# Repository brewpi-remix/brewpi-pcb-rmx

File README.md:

# 

*[@LBussy](https://github.com/lbussy)'s forks of the original [BrewPi Project](https://github.com/BrewPi)*.  This project has a new website, please also visit https://www.brewpiremix.com.  All files will remain here, the website is just to make it easier for me to keep current information available.

# BrewPi Remix Printed Circuit Board Eagle Files

This repository contains the Eagle files for printed circuit boards supporting [BrewPi Remix](https://www.brewpi.com/this-is-brewpi-0-2/).

## Boards Provided
Within this repository are:

- ESP8266 Boards (Supporting @Thorrak's [ESP8266 BrewPi Controllers](https://github.com/thorrak/brewpi-esp8266))
  - Wemos D1 breakout supporting BrewPi Remix or Fermentrack using @Thorrak's [ESP8266 firmware](https://github.com/thorrak/brewpi-esp8266)
  - RJ-45 breakout board, supporting ESP8266 controllers connected via straight-throgh RJ-45 (i,e, Ethernet) cables
- Arduino Uno shield supporting BrewPi Remix RevC as well as I2C
  - Rotary Encoder breakout to facilitate connecting a rotary encoder with DuPont wires
  - Breakout board, mostly for bench work, providing all possible connections via screw terminals as well as DuPont connections, plus heat/cool LED indicators

## Boards Manufacture
You may order boards for manufacture directly from these links:
- Arduino Shield [From PCBs.io](https://PCBs.io/share/zdeBw)
- Wemos D1 breakout [From PCBs.io](https://PCBs.io/share/z5JLZ)
- Breakout Board [From PCBs.io](https://PCBs.io/share/zvpLA)
- Rotary Encoder Breakout Board [From PCBs.io](https://PCBs.io/share/rJPlG)

## Modifying These Files
If you would like to personalize these board designs, you may modify them with [Autodesk's EAGLE](https://www.autodesk.com/products/eagle/overview). EAGLE is a scriptable electronic design automation (EDA) application with schematic capture, printed circuit board (PCB) layout, auto-router and computer-aided manufacturing (CAM) features. EAGLE stands for Easily Applicable Graphical Layout Editor and is developed by CadSoft Computer GmbH. The company was acquired by Autodesk Inc. in 2016.  

The program supports Windows, Linux, and Mac OS X.  EAGLE is available in a [free version](https://www.autodesk.com/products/eagle/free-download), as well as a [subscription-based version with more features](https://www.autodesk.com/products/eagle/compare).

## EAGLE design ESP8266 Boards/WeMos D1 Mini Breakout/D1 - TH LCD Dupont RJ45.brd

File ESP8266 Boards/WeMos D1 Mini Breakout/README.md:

# 

# Wemos D1 Mini BrewPi Breakout

A Wemos D1 Mini breakout board for BrewPi-derivative ESP8266 projects. No third-party level shifter is required.  Through-hole components only for ease of assembly.

[Order from OshPark](https://oshpark.com/shared_projects/YLXZEzde):

- 2 layer board of 1.74 x 1.74 inches (44.2 x 44.1 mm) 
- $15.10 per set of 3

| Top View          | Bottom View          |
| ----------------- |:--------------------:|
| ![Board Top][top] | ![Board Bottom][bot] |

[top]: Top.png "Board Top"
[bot]: Bottom.png "Board Bottom"

## BOM (controller/shield only):

- 1 x [PCB Shield](https://oshpark.com/shared_projects/YLXZEzde) (this project)
- 1 x [Wemos D1 Mini](https://www.aliexpress.com/item/32688079351.html?spm=a2g0o.productlist.0.0.2dcf3152g4UkxV&algo_pvid=be694029-b1d5-44b7-b733-20b8c0f6ba9a&algo_expid=be694029-b1d5-44b7-b733-20b8c0f6ba9a-0&btsid=3b4ec2af-8a5e-4c59-9e85-bb2bdb771ffd&ws_ab_test=searchweb0_0,searchweb201602_1,searchweb201603_52_) (U1)
- 2 x Male 8-pin header (comes with controller)
- 2 x Female 8-pin header (comes with controller)
- 2 x [1.0uF Capacitor](https://www.mouser.com/ProductDetail/KEMET/C320C105K5R5TA?qs=sGAEpiMZZMt3KoXD5rJ2N0CWo9MbFM%2FuWljjm75KZzs%3D) (C1, C3)
- 2 x [0.1uF Capacitor](https://www.mouser.com/ProductDetail/KEMET/C320C104K3R5TA?qs=sGAEpiMZZMt3KoXD5rJ2N4ZXb0dQpKOeXkTyt%2FbcGss%3D) (C2, C4)
- 2 x [2N7000 N-Channel MOSFET](https://www.mouser.com/ProductDetail/ON-Semiconductor/2N7000?qs=sGAEpiMZZMshyDBzk1%2FWi9bHELEahoDnY1fyKF6A6Ko%3D) (Q1, Q2)
- 5 x [10kΩ 1/4-Watt Resistor](https://www.mouser.com/ProductDetail/KOA-Speer/CF1-4CT52R103J?qs=sGAEpiMZZMtlubZbdhIBIG%252BgbQse942Boczpyiowqgc%3D) (R1-R4)
- 1 x [2.2kΩ 1/4-Watt Resistor](https://www.mouser.com/ProductDetail/KOA-Speer/CF1-4CT52R222J?qs=sGAEpiMZZMu61qfTUdNhGx20sZYqUI%252BADLaC9a%252B2%2Flg%3D) (R5)
- 1 x [Wago 2-terminal Screw Clamp](https://www.aliexpress.com/item/32700056337.html) (PWR)
- 1 x [RJ45 Modular Jack w/no shield](https://www.aliexpress.com/item/32736146888.html) (J1)
- 2 x [4-pin DuPont Header](https://www.aliexpress.com/item/32670112443.html?spm=a2g0o.productlist.0.0.b4045bcffb2Q4C&algo_pvid=e9508115-148b-4d72-a7a3-4e45d189d5c7&algo_expid=e9508115-148b-4d72-a7a3-4e45d189d5c7-12&btsid=35f3875d-d1f0-4b92-9a59-406a3faaa4ef&ws_ab_test=searchweb0_0,searchweb201602_1,searchweb201603_52) (RELAY, LCD)
- 1 x [3-pin DuPont Header](https://www.aliexpress.com/item/32670112443.html?spm=a2g0o.productlist.0.0.b4045bcffb2Q4C&algo_pvid=e9508115-148b-4d72-a7a3-4e45d189d5c7&algo_expid=e9508115-148b-4d72-a7a3-4e45d189d5c7-12&btsid=35f3875d-d1f0-4b92-9a59-406a3faaa4ef&ws_ab_test=searchweb0_0,searchweb201602_1,searchweb201603_52) (PWR)
- 1 x [2-pin DuPont Header](https://www.aliexpress.com/item/32670112443.html?spm=a2g0o.productlist.0.0.b4045bcffb2Q4C&algo_pvid=e9508115-148b-4d72-a7a3-4e45d189d5c7&algo_expid=e9508115-148b-4d72-a7a3-4e45d189d5c7-12&btsid=35f3875d-d1f0-4b92-9a59-406a3faaa4ef&ws_ab_test=searchweb0_0,searchweb201602_1,searchweb201603_52) (PWR)

## Board Manufacture

You may order this board for manufacture directly from [PCBs.io](https://PCBs.io/share/z5JLZ).

## 3D-Printed Case

See [this case](https://www.thingiverse.com/thing:2874176) from Thorrak for a case you can print.

## Modifying These Files

If you would like to personalize these board designs, you may modify them with [Autodesk's EAGLE](https://www.autodesk.com/products/eagle/overview). EAGLE is a scriptable electronic design automation (EDA) application with schematic capture, printed circuit board (PCB) layout, auto-router and computer-aided manufacturing (CAM) features. EAGLE stands for Easily Applicable Graphical Layout Editor and is developed by CadSoft Computer GmbH. The company was acquired by Autodesk Inc. in 2016.  

The program supports Windows, Linux, and Mac OS X.  EAGLE is available in a [free version](https://www.autodesk.com/products/eagle/free-download), as well as a [subscription-based version with more features](https://www.autodesk.com/products/eagle/compare).

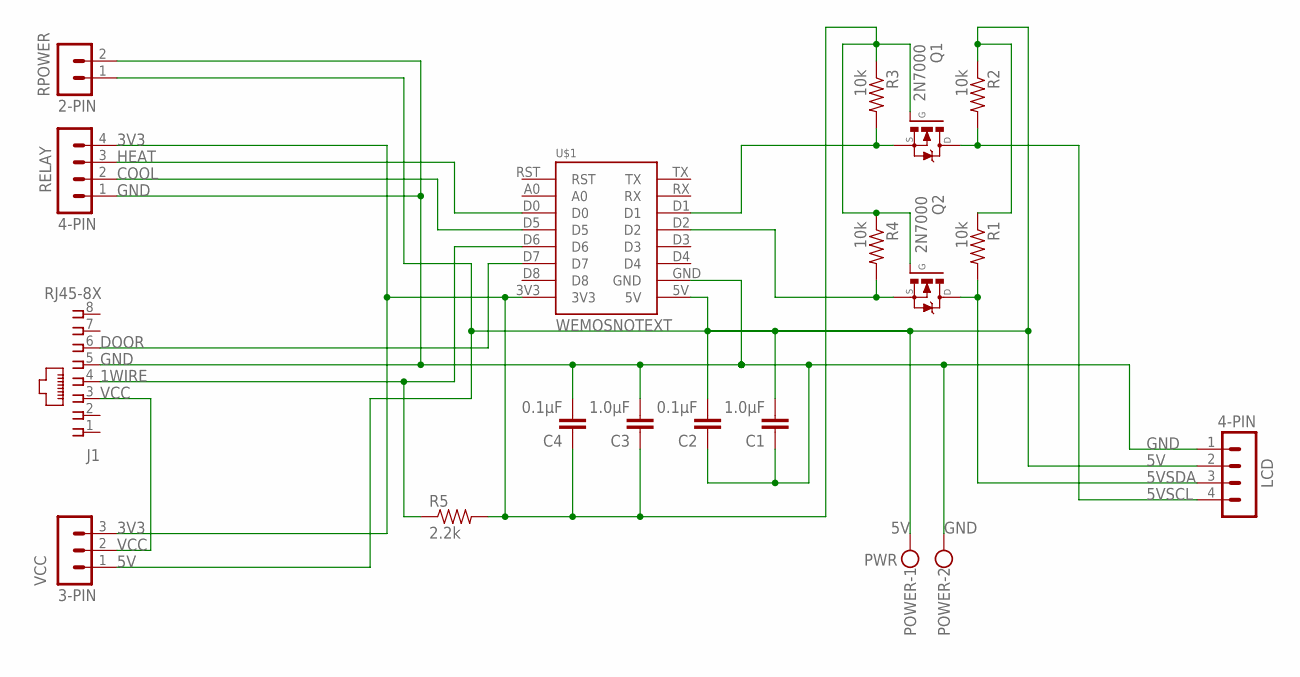
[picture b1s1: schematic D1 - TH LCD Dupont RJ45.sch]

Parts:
C1, C3: 1.0μF; CAP_PTH-2.54
C2, C4: 0.1μF; CAP_PTH-2.54
J1: RJ45-8X; RJ45-NO-SHIELD-NOLINE
LCD: 4-PIN; HDR-4_VERT
POWER: PWR; W237-102
Q1, Q2: 2N7000; TO-92
R1, R2, R3, R4: 10k; AXIAL-0.3
R5: 2.2k; AXIAL-0.3
RELAY: 4-PIN; HDR-4_VERT
RPOWER: 2-PIN; HDR-2_VERT
U$1: WEMOSNOTEXT; WEMOS_D1-NOTEXT
VCC: 3-PIN; MA03-1

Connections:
1WIRE: J1.4, R5.P$1 (1), U$1.D6
3V3: C3.1, C4.1, Q1.2 (G), Q2.2 (G), R3.P$1 (1), R4.P$1 (1), R5.P$2 (2), RELAY.4, U$1.3V3, VCC.3
3VSCL: Q1.1 (S), R3.P$2 (2), U$1.D1
3VSDA: Q2.1 (S), R4.P$2 (2), U$1.D2
5V: C1.2, C2.2, LCD.2, POWER.1, R1.P$1 (1), R2.P$1 (1), RPOWER.1, U$1.5V, VCC.1
5VSCL: LCD.4, Q1.3 (D), R2.P$2 (2)
5VSDA: LCD.3, Q2.3 (D), R1.P$2 (2)
COOL: RELAY.2, U$1.D5
DOOR: J1.6, U$1.D7
GND: C1.1, C2.1, C3.2, C4.2, J1.5, LCD.1, POWER.2, RELAY.1, RPOWER.2, U$1.GND
HEAT: RELAY.3, U$1.D0
VCC: J1.3, VCC.2

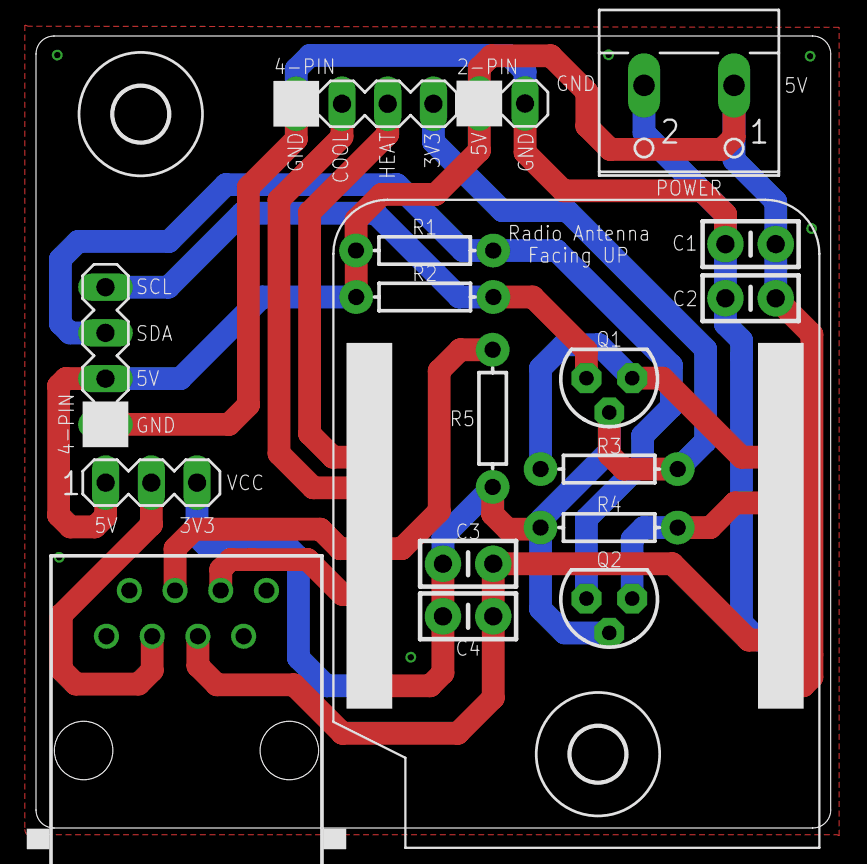
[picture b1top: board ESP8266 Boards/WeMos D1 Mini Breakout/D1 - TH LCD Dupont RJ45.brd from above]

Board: 2 copper layers, 44.1 x 44.0 mm, 20 parts (0 on the bottom side), 12 nets.

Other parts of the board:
U$2, U$4: 3,0

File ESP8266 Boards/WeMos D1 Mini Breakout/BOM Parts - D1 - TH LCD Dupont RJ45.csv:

"Part";"Value";"Device";"Package";"Description";"MF";"MPN";"OC_FARNELL";"OC_NEWARK";"POPULARITY";"PROD_ID";"VALUE";
"C1";"1.0μF";"CAP_CERAMIC_2.54";"CAP_PTH-2.54";"";"";"";"";"";"";"";"";
"C2";"0.1μF";"CAP_CERAMIC_2.54";"CAP_PTH-2.54";"";"";"";"";"";"";"";"";
"C3";"1.0μF";"CAP_CERAMIC_2.54";"CAP_PTH-2.54";"";"";"";"";"";"";"";"";
"C4";"0.1μF";"CAP_CERAMIC_2.54";"CAP_PTH-2.54";"";"";"";"";"";"";"";"";
"J1";"RJ45-8X";"RJ45-8X";"RJ45-NO-SHIELD-NOLINE";"CORCOM Modular RJ Jacks No Shield";"";"RJ45-8X";"unknown";"16R6101";"";"";"";
"LCD";"4-PIN";"HDR-4";"HDR-4_VERT";"PIN HEADER";"";"";"";"";"";"";"";
"POWER";"PWR";"W237-102";"W237-102";"WAGO SCREW CLAMP";"";"237-102";"unknown";"70K9898";"";"";"";
"Q1";"2N7000";"2N7000";"TO-92";"";"";"";"";"";"";"";"";
"Q2";"2N7000";"2N7000";"TO-92";"";"";"";"";"";"";"";"";
"R1";"10k";"10KOHM-HORIZ-1/4W-1%";"AXIAL-0.3";"10kΩ resistor";"";"";"";"";"";"RES-12183";"10k";
"R2";"10k";"10KOHM-HORIZ-1/4W-1%";"AXIAL-0.3";"10kΩ resistor";"";"";"";"";"";"RES-12183";"10k";
"R3";"10k";"10KOHM-HORIZ-1/4W-1%";"AXIAL-0.3";"10kΩ resistor";"";"";"";"";"";"RES-12183";"10k";
"R4";"10k";"10KOHM-HORIZ-1/4W-1%";"AXIAL-0.3";"10kΩ resistor";"";"";"";"";"";"RES-12183";"10k";
"R5";"2.2k";"10KOHM-HORIZ-1/4W-1%";"AXIAL-0.3";"10kΩ resistor";"";"";"";"";"";"RES-12183";"10k";
"RELAY";"4-PIN";"HDR-4";"HDR-4_VERT";"PIN HEADER";"";"";"";"";"";"";"";
"RPOWER";"2-PIN";"HDR-2";"HDR-2_VERT";"";"";"";"";"";"";"";"";
"U$1";"WEMOSNOTEXT";"WEMOSNOTEXT";"WEMOS_D1-NOTEXT";"";"";"";"";"";"";"";"";
"VCC";"3-PIN";"MA03-1";"MA03-1";"PIN HEADER";"";"";"unknown";"unknown";"48";"";"";

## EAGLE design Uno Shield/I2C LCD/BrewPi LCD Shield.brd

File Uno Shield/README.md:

# 

# BrewPi Arduino Uno Shield v1.3.1a (I2C/Parallel LCD)

Arduino Uno shield for the [BrewPi Remix](https://www.brewpiremix.com) project. This is an new board design which incorporates an I2C LCD header in addition to the original parallel LCD header on the RevC.  The I2C display is supported in version 0.5.3 of BrewPi Legacy Remix Scripts, WWW and Tools, coupled with version 0.2.12 of the Arduino Firmware.

[Order from PCBs.io](https://PCBs.io/share/zdeBw):

- 2 Layer Board - 5.1164 sq in (2.1200in x 2.4134in) / 3300.9 sq/mm (53.85mm x 61.3mm)
- $19.39 per set of 4 ($3.79 per sq in)

## Supported Features:

  * Wireless to Serial Bridge (Bluetooth or ESP8266 module)
  * Door switch
  * Alarm
  * Heat/Cool Relay
  * Rotary Encoder w/Pushbutton
  * Heat/Cool LEDs
  * OneWire Selector A0/A4 (required for I2C)
  * Three OneWire connections
  * I2C LCD; or;
  * Parallel LCD
  * RJ45 connector includes support for:
    * OneWire
    * Door Switch
    * Heat/Cool Relay
  * All Arduino headers available

## Usage Notes:
Since this board is intended to support both the RevC as well as the I2C firmware, some configuration is required via jumper caps.

  - ONE_WIRE_SEL Jumper - If you do not select the proper configuration, you may not be able to configure the OneWire sensors, the display may fault, or both.
    - Jump between A4 and the center pin for RevC
    - Jump between A0 and the center pin for I2C
  - Backlight Timeout - If you do not have a rotary encoder you will not be able to wake the backlight if it times out.  You can configure the board to never turn off the backlight
    - RevC - The BACKLIGHT jumper has two settings:
      - Jump between ON and the center pin to have the backlight stay on
      - Jump between PB and the center pin to have the backlight time out
    - I2C - The backlight setting uses the rotary encoder header
      - If you have a rotary encoder, pushing the button during a controller reset will disable backlight timer
      - If you do not have a rotary encoder, adding a jumper on the ROT_ENC header between PSH and GND will disable backlight timer
  - Heat / Cool LEDs - You will use different connections for LEDs depending on the configuration of your actuators
    - Inverted (typical for relay board) - Connect the LED between VCC and the center pin.  A resistor is not needed as there is one on the board
    - Non-Inverted (typical for SSRs) - Connect the LED between the center pin and GND.  A resistor is not needed as there is one on the board

## BOM:

  * From Mouser (by using [this link](https://www.mouser.com/ProjectManager/ProjectDetail.aspx?AccessID=d74098d8b5) you can view all of these parts on Mouser and simply click the "Order Project" button):
    * 7 ea [0.1μF Ceramic Capacitor](https://www.mouser.com/ProductDetail/?qs=PmkNt%2FFLxQc4kNUCHU6a6Q%3D%3D) (C1-7)
    * 1 ea [1.0μF Ceramic Capacitor](https://www.mouser.com/ProductDetail/?qs=AQlKX63v8RtdX%2FUKFBhcig%3D%3D) (C8)
    * 1 ea [10kΩ Trimmer Resistor](https://www.mouser.com/ProductDetail/?qs=V3Em1enZyNPGF2%252BnCaKTKw%3D%3D) (R1)
    * 4 ea [10kΩ Axial Resistor 1/4W](https://www.mouser.com/ProductDetail/?qs=AtFvwFU%2F1FmCMXRebRRiVA%3D%3D) (R3-5, 12)
    * 1 ea [150Ω Axial Resistor 1/4W](https://www.mouser.com/ProductDetail/?qs=7jyBjEprRBipjkz1NPmruA%3D%3D) (R11)
    * 1 ea [1kΩ Axial Resistor 1/4W](https://www.mouser.com/ProductDetail/?qs=ddCg%252BR5cWn2sqOoxwN8P1g%3D%3D) (R8)
    * 1 ea [20kΩ Axial Resistor 1/4W](https://www.mouser.com/ProductDetail/KOA-Speer/MF1-4CC2002F?qs=sGAEpiMZZMu61qfTUdNhG%2Fir46E4ZSr2LQlauiwvExA%3D) (R2)
    * 2 ea [220Ω Axial Resistor 1/4W](https://www.mouser.com/ProductDetail/?qs=KVzGhl%2FcVV1aGF8Vc%2F%252BvDg%3D%3D) (R9, 10)
    * 1 ea [2kΩ Axial Resistor 1/4W](https://www.mouser.com/ProductDetail/?qs=iPPgFPFs9PM72iUDc08rBg%3D%3D) (R7)
    * 1 ea [4.7kΩ Axial Resistor 1/4W](https://www.mouser.com/ProductDetail/?qs=WbbykRgge7o4TK6QsdXS5A%3D%3D) (R6)
    * 1 ea [2N3906 PNP Transistor](https://www.mouser.com/ProductDetail/?qs=iN0KuJO79Kbn9o7a2lB4uA%3D%3D) (Q1)
    * 1 ea [SN74HC595N 8-Bit Shift Register](https://www.mouser.com/ProductDetail/?qs=IEl3ej0IqwBTHkYa8XPoMQ%3D%3D) (U1)
    * 1 ea [16-pin IC Socket](https://www.mouser.com/ProductDetail/?qs=5aG0NVq1C4zi9nx%252BGroISQ%3D%3D) (U1)
  * From Adafruit:
    * [Shield stacking headers for Arduino](https://www.adafruit.com/product/85)
    * [Break-away 0.1" 36-pin strip male header - Black - 10 pack](https://www.adafruit.com/product/392), more than enough for:
      * 2 ea 2-pin Header 2.54mm pitch (or 1 ea 4 pin)
      * 7 ea 3-pin Header 2.54mm pitch
      * 4 ea 4-pin Header 2.54mm pitch
      * 2 ea 6-pin Header 2.54mm pitch
  * 2 ea [Jumper Cap](https://www.amazon.com/ZYAMY-2-54mm-Standard-Circuit-Connection/dp/B077957RN7) (or you can use a female/female Dupont jumpers but caps are definitely better looking)
  * 1 ea [RJ45 Socket](https://www.aliexpress.com/item/High-Quality-20pcs-RJ45-8P8C-Computer-Internet-Network-PCB-Jack-Socket-Black/32736146888.html)

Other items you may want in order to complete your project:

  * LCD Display, either;
    * [20x4 LCD Parallel](https://www.amazon.com/SunFounder-Serial-Module-Arduino-Mega2560/dp/B071W8SW9R), or;
    * [20x4 LCD I2C](https://www.amazon.com/SunFounder-Serial-Module-Arduino-Mega2560/dp/B01GPUMP9C)
  * [5v 2-Channel Relay Module](https://www.amazon.com/gp/product/B00TMFVVG6)
  * [Rotary Encoder](https://www.mouser.com/ProductDetail/490-CZ11BR1E15FD120C)  - You want a magnetic encoder, no pull-ups, and 20 detents
  * [Knob for Rotary Encoder](https://www.mouser.com/ProductDetail/Eagle-Plastic-Devices/450-4763?qs=sGAEpiMZZMuiwDVLTMm01an1wsjHLopM%252Bn33k8wqz%252Bs%3D)
  * [Rotary Encoder Breakout Board](https://PCBs.io/share/zkPZ0)
  * At least two [DS18B20 Waterproof Temperature Sensors](https://www.amazon.com/gp/product/B01JKVRVNI)
  * Assorted [Dupont Jumper Wires](https://www.amazon.com/Multicolored-Breadboard-Dupont-Jumper-Wires/dp/B073X7P6N2) (male-male, male-female, female-female)

## Board Manufacture

You may order this board for manufacture directly from [pcbs.io](https://PCBs.io/share/zdeBw).

## 3D-Printed Case

See [this case](https://www.thingiverse.com/thing:3416312) from @gromitdj for a case you can print.

## Modifying These Files
If you would like to personalize these board designs, you may modify them with [Autodesk's EAGLE](https://www.autodesk.com/products/eagle/overview). EAGLE is a scriptable electronic design automation (EDA) application with schematic capture, printed circuit board (PCB) layout, auto-router and computer-aided manufacturing (CAM) features. EAGLE stands for Easily Applicable Graphical Layout Editor and is developed by CadSoft Computer GmbH. The company was acquired by Autodesk Inc. in 2016.  

The program supports Windows, Linux, and Mac OS X.  EAGLE is available in a [free version](https://www.autodesk.com/products/eagle/free-download), as well as a [subscription-based version with more features](https://www.autodesk.com/products/eagle/compare).

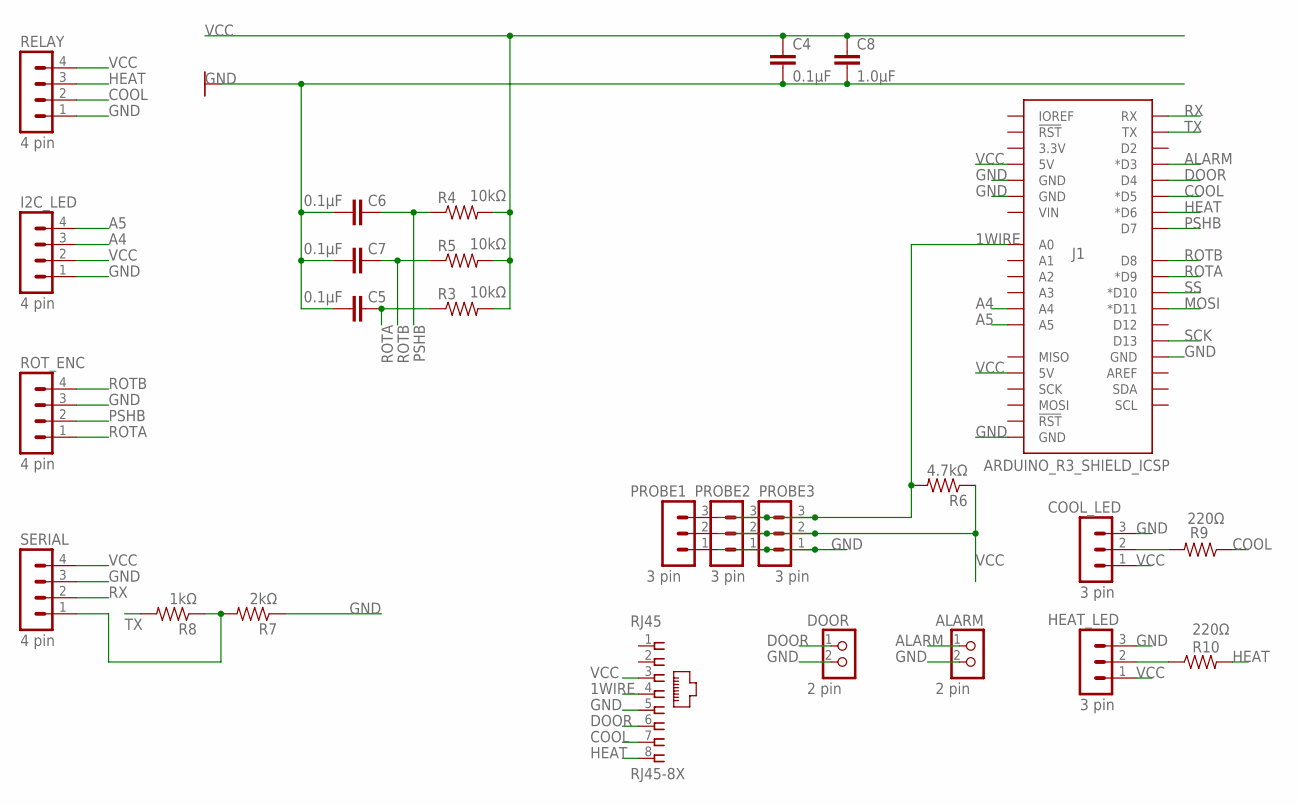
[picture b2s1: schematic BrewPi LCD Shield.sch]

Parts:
ALARM: 2 pin; HEADER02-1
C4, C5, C6, C7: 0.1μF; CAP-PTH-SMALL-KIT
C8: 1.0μF; CAP-PTH-SMALL-KIT
COOL_LED: 3 pin; HEADER03-1
DOOR: 2 pin; HEADER02-1
HEAT_LED: 3 pin; HEADER03-1
I2C_LED: 4 pin; HEADER04-1
J1: ARDUINO_R3_SHIELD_ICSP; UNO_R3_SHIELD_ICSP
PROBE1, PROBE2, PROBE3: 3 pin; HEADER03-1
R3, R4, R5: 10kΩ; AXIAL-0.3
R6: 4.7kΩ; AXIAL-0.3
R7: 2kΩ; AXIAL-0.3
R8: 1kΩ; AXIAL-0.3
R9, R10: 220Ω; AXIAL-0.3
RELAY: 4 pin; HEADER04-1
RJ45: RJ45-8X; RJ45-NO-SHIELD
ROT_ENC: 4 pin; HEADER04-1
SERIAL: 4 pin; HEADER04-1

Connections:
1WIRE: J1.A0, PROBE1.3, PROBE2.3, PROBE3.3, R6.P$2 (2), RJ45.4
A4: I2C_LED.3, J1.A4
A5: I2C_LED.4, J1.A5
ALARM: ALARM.1, J1.D3 (*D3)
COOL: J1.D5 (*D5), R9.P$1 (1), RELAY.2, RJ45.7
DOOR: DOOR.1, J1.D4, RJ45.6
GND: ALARM.2, C4.2, C5.2, C6.2, C7.2, C8.2, COOL_LED.3, DOOR.2, HEAT_LED.3, I2C_LED.1, J1.GND@0 (GND), J1.GND@1 (GND), J1.GND@2 (GND), J1.GND_ICSP (GND), PROBE1.1, PROBE2.1, PROBE3.1, R7.P$1 (1), RELAY.1, RJ45.5, ROT_ENC.3, SERIAL.3
HEAT: J1.D6 (*D6), R10.P$2 (2), RELAY.3, RJ45.8
MOSI: J1.D11 (*D11)
unnamed: R7.P$2 (2), R8.P$1 (1), SERIAL.1
unnamed: COOL_LED.2, R9.P$2 (2)
unnamed: HEAT_LED.2, R10.P$1 (1)
PSHB: C6.1, J1.D7, R4.P$1 (1), ROT_ENC.2
ROTA: C5.1, J1.D9 (*D9), R3.P$1 (1), ROT_ENC.1
ROTB: C7.1, J1.D8, R5.P$1 (1), ROT_ENC.4
RX: J1.RX, SERIAL.2
SCK: J1.D13
SS: J1.D10 (*D10)
TX: J1.TX, R8.P$2 (2)
VCC: C4.1, C8.1, COOL_LED.1, HEAT_LED.1, I2C_LED.2, J1.5V, J1.5V_ICSP (5V), PROBE1.2, PROBE2.2, PROBE3.2, R3.P$2 (2), R4.P$2 (2), R5.P$2 (2), R6.P$1 (1), RELAY.4, RJ45.3, SERIAL.4

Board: 2 copper layers, 26 parts (0 on the bottom side), 17 nets, no tracks yet.

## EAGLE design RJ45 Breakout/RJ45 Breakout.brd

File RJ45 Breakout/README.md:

# 

Make or buy?  That is the question.  Since providing the below listed DIY breakout, I found these on Amazon (of course!):

- [Four-Way RJ45 Breakout Board](https://smile.amazon.com/Electronics-Salon-4-Way-Breakout-Terminal-Connector/dp/B01GNOBDPM)
- [RJ45 Ethernet Splitter (2-way)](https://smile.amazon.com/Splitter-Connectors-Ethernet-Interface-Internet/dp/B07CW7JHYV)
- [RJ45 Ethernet Splitter (3-way)](https://smile.amazon.com/Ethernet-Splitter-vienon-Adapter-Connector/dp/B0932B8JGJ)

I have the below setup in all my fermenters, but I have to say I might be tempted to use these if I had to do it again.

Note: These links are NOT affiliat elinks but are pointing to [smile.amazon.com](https://smile.amazon.com/gp/chpf/about/).  If you are not currently enrolled in this program, you should at least review the link.  It's an easy way to support your favorite charity every time you shop on Amazon.  If you are at a loss to pick a charity, may I suggest the [Wounded Warrior Project](https://www.woundedwarriorproject.org/)?

If you are interested in building a splitter, here's one way to go:

# RJ-45 Sensor Breakout

A breakout board created to connect sensors and the door switch via an RJ-45 straight-through cable (i.e. Ethernet.)

[Order from PCBs.io](#):

- 2 Layer Board - 0.7087 sq in (0.7038in x 1.0069in) / 457.22 sq/mm (17.88mm x 25.58mm)
- $2.83 per set of 4 ($4.00 per sq in)

| Top View          | Bottom View          |
| ----------------- |:--------------------:|
| ![Board Top][top] | ![Board Bottom][bot] |

[top]: Top.png "Board Top"
[bot]: Bottom.png "Board Bottom"

BOM:

- 1 x [PCB Breakout](#) (this project)
- 1 x [Wago 2-terminal Screw Clamp](https://www.aliexpress.com/item/32700056337.html) (X1)
- 3 x [Wago 3-terminal Screw Clamp](#) (X1)
- 1 x [RJ45 Modular Jack w/no shield](https://www.aliexpress.com/item/32736146888.html) (J1)

## Board Manufacture

You may order this board for manufacture directly from [PCBs.io](https://PCBs.io/share/rJPlG).

## 3D-Printed Case

See [this case](#) from Thorrak for a case you can print.

## Modifying These Files

If you would like to personalize these board designs, you may modify them with [Autodesk's EAGLE](https://www.autodesk.com/products/eagle/overview). EAGLE is a scriptable electronic design automation (EDA) application with schematic capture, printed circuit board (PCB) layout, auto-router and computer-aided manufacturing (CAM) features. EAGLE stands for Easily Applicable Graphical Layout Editor and is developed by CadSoft Computer GmbH. The company was acquired by Autodesk Inc. in 2016.  

The program supports Windows, Linux, and Mac OS X.  EAGLE is available in a [free version](https://www.autodesk.com/products/eagle/free-download), as well as a [subscription-based version with more features](https://www.autodesk.com/products/eagle/compare).

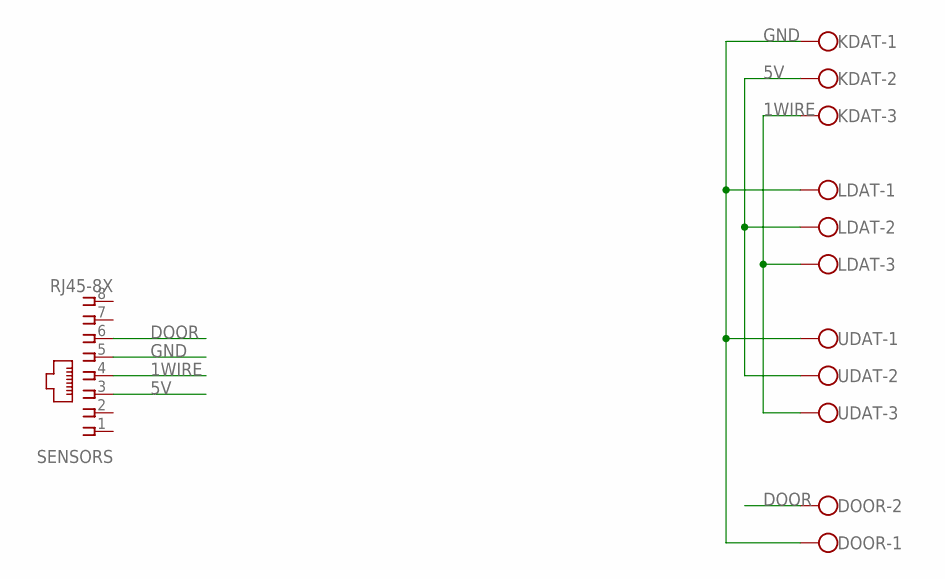
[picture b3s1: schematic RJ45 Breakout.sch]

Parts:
DOOR: W237-102
KDAT: W237-103
LDAT: W237-103
SENSORS: RJ45-8X; RJ45-NO-SHIELD
UDAT: W237-103

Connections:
1WIRE: KDAT.3, LDAT.3, SENSORS.4, UDAT.3
5V: KDAT.2, LDAT.2, SENSORS.3, UDAT.2
DOOR: DOOR.2, SENSORS.6
GND: DOOR.1, KDAT.1, LDAT.1, SENSORS.5, UDAT.1

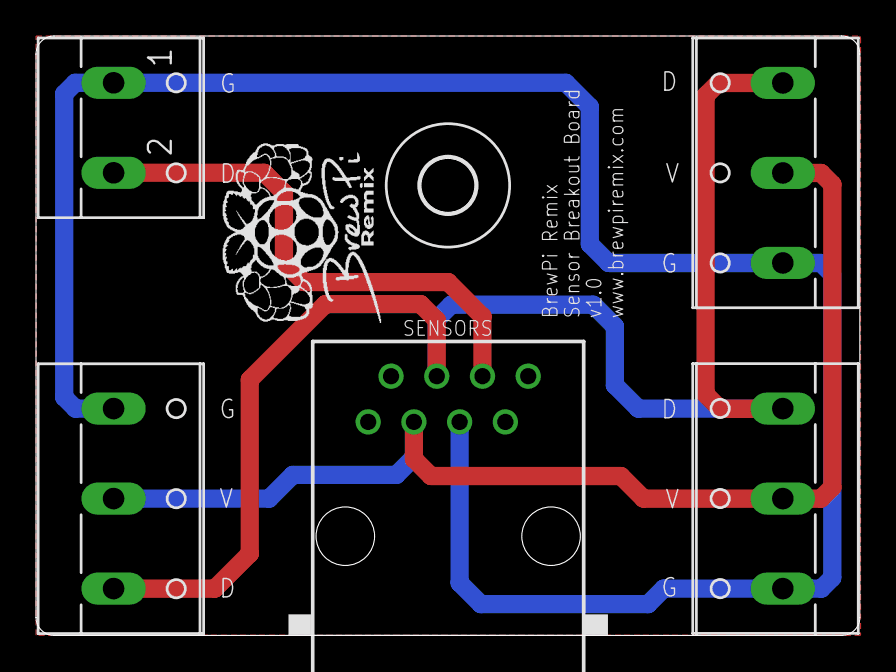
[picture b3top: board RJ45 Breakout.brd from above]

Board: 2 copper layers, 45.8 x 33.3 mm, 6 parts (0 on the bottom side), 4 nets.

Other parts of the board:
U$1: 3,0

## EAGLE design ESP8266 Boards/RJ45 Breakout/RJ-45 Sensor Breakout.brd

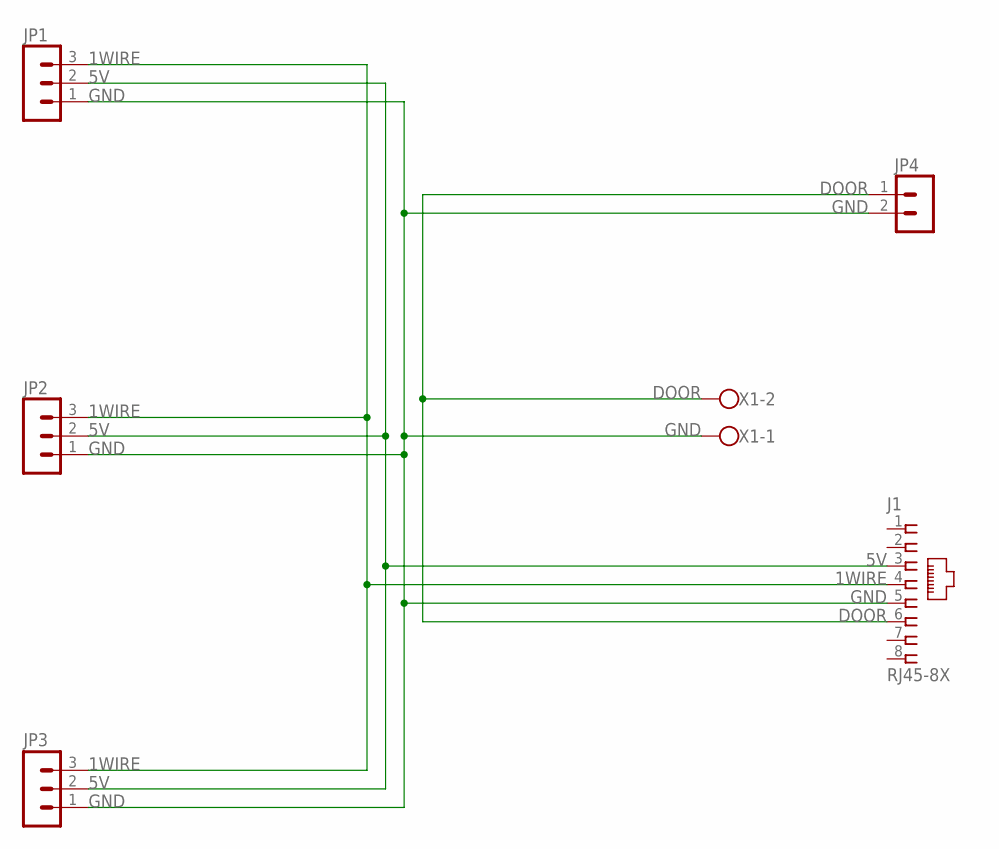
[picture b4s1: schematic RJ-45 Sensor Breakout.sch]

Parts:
J1: RJ45-8X; RJ45-NO-SHIELD-NOLINE
JP1, JP2: HDR-3_VERT
JP3: OneWire; HDR-3_VERT
JP4: HDR-2; HDR-2_VERT
X1: W237-102

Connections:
1WIRE: J1.4, JP1.3, JP2.3, JP3.3
5V: J1.3, JP1.2, JP2.2, JP3.2
DOOR: J1.6, JP4.1, X1.2
GND: J1.5, JP1.1, JP2.1, JP3.1, JP4.2, X1.1

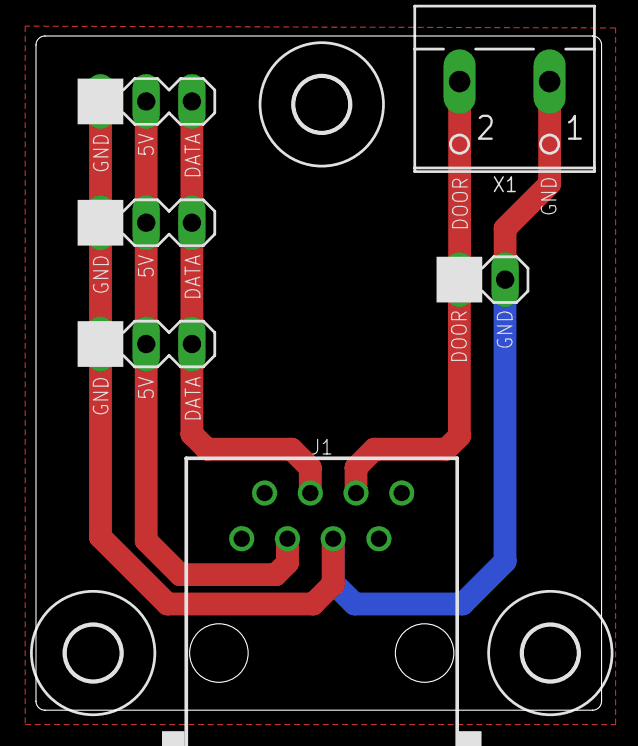
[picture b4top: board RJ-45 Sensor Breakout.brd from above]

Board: 2 copper layers, 31.4 x 37.5 mm, 9 parts (0 on the bottom side), 4 nets.

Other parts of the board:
U$1, U$2, U$3: 3,0

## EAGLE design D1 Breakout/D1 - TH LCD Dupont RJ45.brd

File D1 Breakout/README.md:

# 

# Wemos D1 Mini BrewPi Breakout

A Wemos D1 Mini breakout board for BrewPi-derivative ESP8266 projects. No third-party level shifter is required.  Through-hole components only for ease of assembly.

[Order from PCBs.io](https://PCBs.io/share/z5JLZ):

- 2 Layer Board - 0.7087 sq in (0.7038in x 1.0069in) / 457.22 sq/mm (17.88mm x 25.58mm)
- $2.83 per set of 4 ($4.00 per sq in)

| Top View          | Bottom View          |
| ----------------- |:--------------------:|
| ![Board Top][top] | ![Board Bottom][bot] |

[top]: Top.png "Board Top"
[bot]: Bottom.png "Board Bottom"

## BOM (controller/shield only):

- 1 x [PCB Shield](https://PCBs.io/share/z5JLZ) (this project)
- 1 x [Wemos D1 Mini](https://www.aliexpress.com/item/32688079351.html?spm=a2g0o.productlist.0.0.2dcf3152g4UkxV&algo_pvid=be694029-b1d5-44b7-b733-20b8c0f6ba9a&algo_expid=be694029-b1d5-44b7-b733-20b8c0f6ba9a-0&btsid=3b4ec2af-8a5e-4c59-9e85-bb2bdb771ffd&ws_ab_test=searchweb0_0,searchweb201602_1,searchweb201603_52_) (U1)
- 2 x Male 8-pin header (comes with controller)
- 2 x Female 8-pin header (comes with controller)
- 2 x [1.0uF Capacitor](https://www.mouser.com/ProductDetail/KEMET/C320C105K5R5TA?qs=sGAEpiMZZMt3KoXD5rJ2N0CWo9MbFM%2FuWljjm75KZzs%3D) (C1, C3)
- 2 x [0.1uF Capacitor](https://www.mouser.com/ProductDetail/KEMET/C320C104K3R5TA?qs=sGAEpiMZZMt3KoXD5rJ2N4ZXb0dQpKOeXkTyt%2FbcGss%3D) (C2, C4)
- 2 x [2N7000 N-Channel MOSFET](https://www.mouser.com/ProductDetail/ON-Semiconductor/2N7000?qs=sGAEpiMZZMshyDBzk1%2FWi9bHELEahoDnY1fyKF6A6Ko%3D) (Q1, Q2)
- 5 x [10kΩ 1/4-Watt Resistor](https://www.mouser.com/ProductDetail/KOA-Speer/CF1-4CT52R103J?qs=sGAEpiMZZMtlubZbdhIBIG%252BgbQse942Boczpyiowqgc%3D) (R1-R4)
- 1 x [2.2kΩ 1/4-Watt Resistor](https://www.mouser.com/ProductDetail/KOA-Speer/CF1-4CT52R222J?qs=sGAEpiMZZMu61qfTUdNhGx20sZYqUI%252BADLaC9a%252B2%2Flg%3D) (R5)
- 1 x [Wago 2-terminal Screw Clamp](https://www.aliexpress.com/item/32700056337.html) (PWR)
- 1 x [RJ45 Modular Jack w/no shield](https://www.aliexpress.com/item/32736146888.html) (J1)
- 2 x [4-pin DuPont Header](https://www.aliexpress.com/item/32670112443.html?spm=a2g0o.productlist.0.0.b4045bcffb2Q4C&algo_pvid=e9508115-148b-4d72-a7a3-4e45d189d5c7&algo_expid=e9508115-148b-4d72-a7a3-4e45d189d5c7-12&btsid=35f3875d-d1f0-4b92-9a59-406a3faaa4ef&ws_ab_test=searchweb0_0,searchweb201602_1,searchweb201603_52) (RELAY, LCD)
- 1 x [2-pin DuPont Header](https://www.aliexpress.com/item/32670112443.html?spm=a2g0o.productlist.0.0.b4045bcffb2Q4C&algo_pvid=e9508115-148b-4d72-a7a3-4e45d189d5c7&algo_expid=e9508115-148b-4d72-a7a3-4e45d189d5c7-12&btsid=35f3875d-d1f0-4b92-9a59-406a3faaa4ef&ws_ab_test=searchweb0_0,searchweb201602_1,searchweb201603_52) (PWR)

## Board Manufacture

You may order this board for manufacture directly from [PCBs.io](https://PCBs.io/share/z5JLZ).

## 3D-Printed Case

See [this case](https://www.thingiverse.com/thing:2874176) from Thorrak for a case you can print.

## Modifying These Files

If you would like to personalize these board designs, you may modify them with [Autodesk's EAGLE](https://www.autodesk.com/products/eagle/overview). EAGLE is a scriptable electronic design automation (EDA) application with schematic capture, printed circuit board (PCB) layout, auto-router and computer-aided manufacturing (CAM) features. EAGLE stands for Easily Applicable Graphical Layout Editor and is developed by CadSoft Computer GmbH. The company was acquired by Autodesk Inc. in 2016.  

The program supports Windows, Linux, and Mac OS X.  EAGLE is available in a [free version](https://www.autodesk.com/products/eagle/free-download), as well as a [subscription-based version with more features](https://www.autodesk.com/products/eagle/compare).

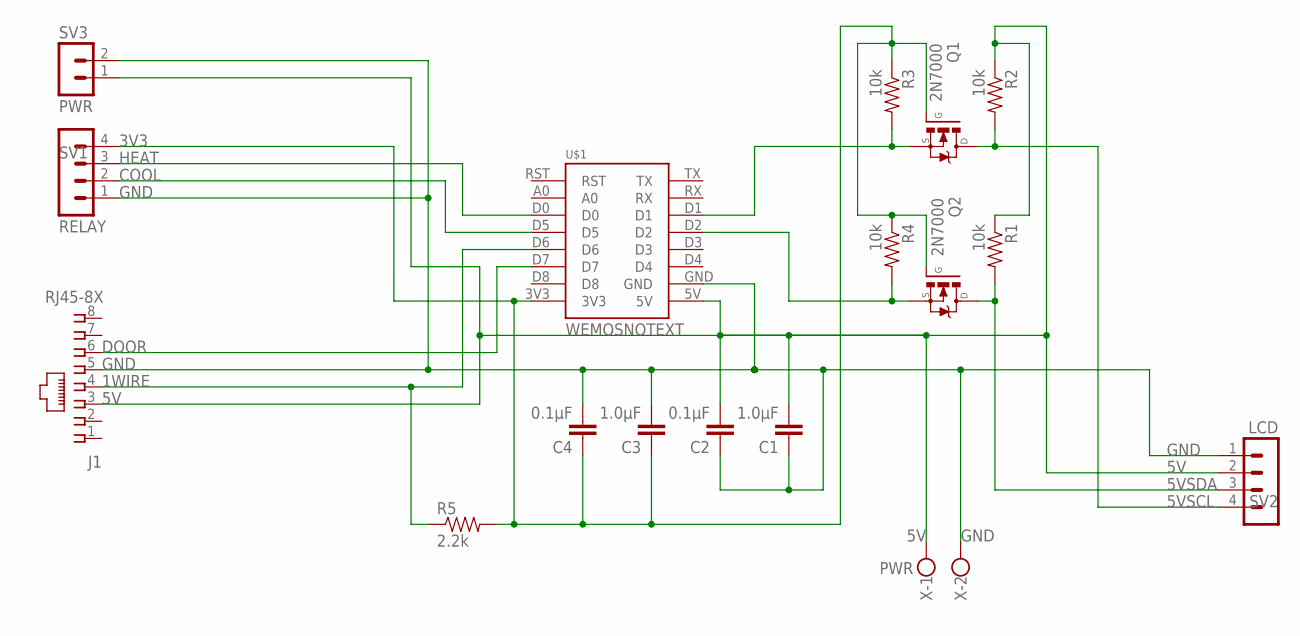
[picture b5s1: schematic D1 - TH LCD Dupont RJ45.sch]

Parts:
C1, C3: 1.0μF; CAP_PTH-2.54
C2, C4: 0.1μF; CAP_PTH-2.54
J1: RJ45-8X; RJ45-NO-SHIELD-NOLINE
Q1, Q2: 2N7000; TO-92
R1, R2, R3, R4: 10k; AXIAL-0.3
R5: 2.2k; AXIAL-0.3
SV1: RELAY; HDR-4_VERT
SV2: LCD; HDR-4_VERT
SV3: PWR; HDR-2_VERT
U$1: WEMOSNOTEXT; WEMOS_D1-NOTEXT
X: PWR; W237-102

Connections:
1WIRE: J1.4, R5.P$1 (1), U$1.D6
3V3: C3.1, C4.1, Q1.2 (G), Q2.2 (G), R3.P$1 (1), R4.P$1 (1), R5.P$2 (2), SV1.4, U$1.3V3
3VSCL: Q1.1 (S), R3.P$2 (2), U$1.D1
3VSDA: Q2.1 (S), R4.P$2 (2), U$1.D2
5V: C1.2, C2.2, J1.3, R1.P$1 (1), R2.P$1 (1), SV2.2, SV3.1, U$1.5V, X.1
5VSCL: Q1.3 (D), R2.P$2 (2), SV2.4
5VSDA: Q2.3 (D), R1.P$2 (2), SV2.3
COOL: SV1.2, U$1.D5
DOOR: J1.6, U$1.D7
GND: C1.1, C2.1, C3.2, C4.2, J1.5, SV1.1, SV2.1, SV3.2, U$1.GND, X.2
HEAT: SV1.3, U$1.D0

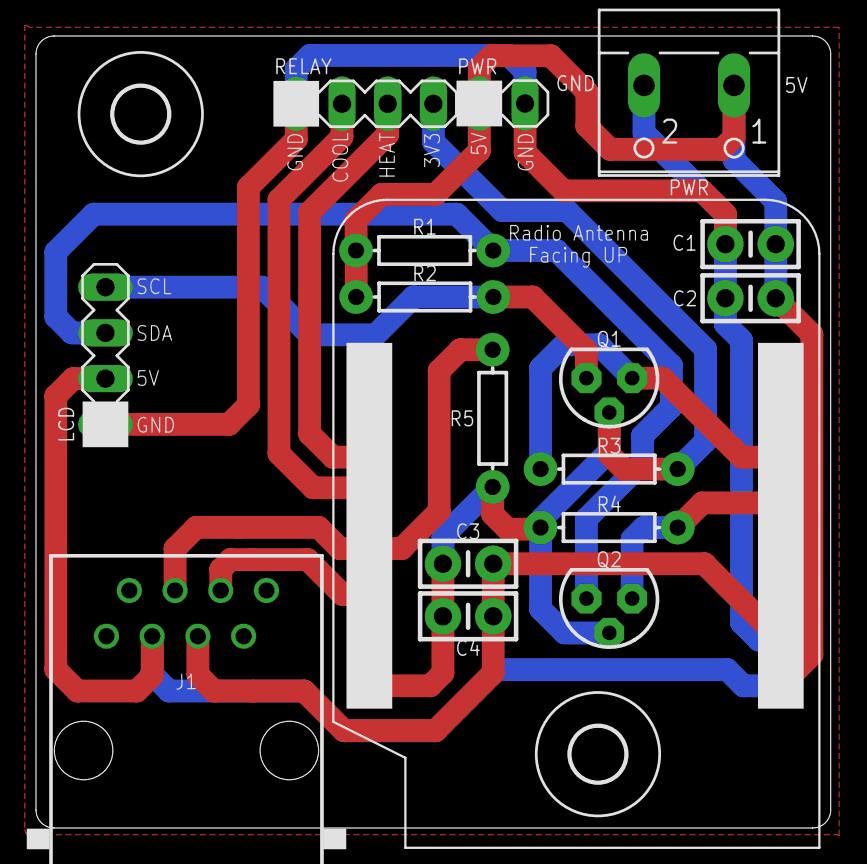
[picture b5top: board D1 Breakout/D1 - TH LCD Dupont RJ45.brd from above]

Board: 2 copper layers, 44.1 x 44.0 mm, 19 parts (0 on the bottom side), 11 nets.

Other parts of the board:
U$2, U$4: 3,0

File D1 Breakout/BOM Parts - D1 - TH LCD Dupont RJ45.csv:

"Part";"Value";"Device";"Package";"Description";"MF";"MPN";"OC_FARNELL";"OC_NEWARK";"PROD_ID";"VALUE";
"C1";"1.0μF";"CAP_CERAMIC_2.54";"CAP_PTH-2.54";"";"";"";"";"";"";"";
"C2";"0.1μF";"CAP_CERAMIC_2.54";"CAP_PTH-2.54";"";"";"";"";"";"";"";
"C3";"1.0μF";"CAP_CERAMIC_2.54";"CAP_PTH-2.54";"";"";"";"";"";"";"";
"C4";"0.1μF";"CAP_CERAMIC_2.54";"CAP_PTH-2.54";"";"";"";"";"";"";"";
"J1";"RJ45-8X";"RJ45-8X";"RJ45-NO-SHIELD-NOLINE";"CORCOM Modular RJ Jacks No Shield";"";"RJ45-8X";"unknown";"16R6101";"";"";
"Q1";"2N7000";"2N7000";"TO-92";"";"";"";"";"";"";"";
"Q2";"2N7000";"2N7000";"TO-92";"";"";"";"";"";"";"";
"R1";"10k";"10KOHM-HORIZ-1/4W-1%";"AXIAL-0.3";"10kΩ resistor";"";"";"";"";"RES-12183";"10k";
"R2";"10k";"10KOHM-HORIZ-1/4W-1%";"AXIAL-0.3";"10kΩ resistor";"";"";"";"";"RES-12183";"10k";
"R3";"10k";"10KOHM-HORIZ-1/4W-1%";"AXIAL-0.3";"10kΩ resistor";"";"";"";"";"RES-12183";"10k";
"R4";"10k";"10KOHM-HORIZ-1/4W-1%";"AXIAL-0.3";"10kΩ resistor";"";"";"";"";"RES-12183";"10k";
"R5";"2.2k";"10KOHM-HORIZ-1/4W-1%";"AXIAL-0.3";"10kΩ resistor";"";"";"";"";"RES-12183";"10k";
"SV1";"RELAY";"HDR-4";"HDR-4_VERT";"PIN HEADER";"";"";"";"";"";"";
"SV2";"LCD";"HDR-4";"HDR-4_VERT";"PIN HEADER";"";"";"";"";"";"";
"SV3";"PWR";"HDR-2";"HDR-2_VERT";"";"";"";"";"";"";"";
"U$1";"WEMOSNOTEXT";"WEMOSNOTEXT";"WEMOS_D1-NOTEXT";"";"";"";"";"";"";"";
"X";"PWR";"W237-102";"W237-102";"WAGO SCREW CLAMP";"";"237-102";"unknown";"70K9898";"";"";

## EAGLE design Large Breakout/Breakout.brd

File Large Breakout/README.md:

# 

# BrewPi Breakout v1.3.1a

Breakout Board for the [BrewPi Legacy Remix](https://www.brewpiremix.com) project. This optional breakout board is intended to be connected to the Arduino Shield v1.3.1a via a straight-through RJ45 terminated cable (i.e. an Ethernet cable.)  It allows the Arduino to be located remotely from the fermentation chamber.

[Order from PCBs.io](https://PCBs.io/share/zvpLA):

- 2 Layer Board - 2.3751 sq in (1.2130in x 1.9580in) / 1532.32 sq/mm (30.81mm x 49.73mm)
- $9.38 per set of 4 ($3.95 per sq in)

## Supported Features:

  * Door switch
  * Heat/Cool
    * Dupont pins
    * Screw terminal
  * Heat/Cool LEDs
  * Temp Sensors
    * Three Dupont pin sets
    * Three screw terminals

## Usage Notes:
Since this board is intended to support multiple configurations, some customization during assembly is required.

  - Heat / Cool LEDs - You will use different connections for LEDs depending on the configuration of your actuators.  Connections are provided for two LEDs each for heat and cool, however you will only use one based on your setup
    - Inverted (typical for relay board) - Connect the LED between VCC and the center pin.  A resistor is not needed as there is one on the board
    - Non-Inverted (typical for SSRs) - Connect the LED between the center pin and GND.  A resistor is not needed as there is one on the board

## BOM:

  * 1 ea [Red 3mm LED](https://www.mouser.com/ProductDetail/638-MV5064.MP4B)
  * 1 ea [Blue 3mm LED](https://www.mouser.com/ProductDetail/941-C503BBCNCV0Z0461)
  * 2 ea [220Ω 1/4W Axial Resistors](https://www.mouser.com/ProductDetail/660-MF1-4DCT52R2200F)
  * 1 ea 4-Pin header
  * 1 ea 2-Pin header
  * 3 ea 3-Pin headers
  * 1 ea RJ45 terminal
  * 3 ea 3-Position screw terminal
  * 1 ea 4-Position screw terminal
  * 1 ea 2-Position screw terminal

## Board Manufacture
You may order this board for manufacture directly from [PCBs.io](https://PCBs.io/share/zvpLA).

## Modifying These Files
If you would like to personalize these board designs, you may modify them with [Autodesk's EAGLE](https://www.autodesk.com/products/eagle/overview). EAGLE is a scriptable electronic design automation (EDA) application with schematic capture, printed circuit board (PCB) layout, auto-router and computer-aided manufacturing (CAM) features. EAGLE stands for Easily Applicable Graphical Layout Editor and is developed by CadSoft Computer GmbH. The company was acquired by Autodesk Inc. in 2016.  

The program supports Windows, Linux, and Mac OS X.  EAGLE is available in a [free version](https://www.autodesk.com/products/eagle/free-download), as well as a [subscription-based version with more features](https://www.autodesk.com/products/eagle/compare).

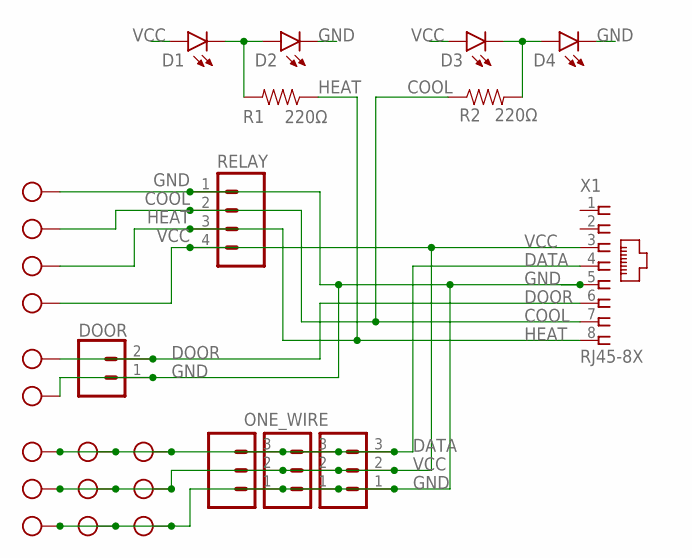
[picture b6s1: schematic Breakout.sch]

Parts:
D1: HINV; LED_3MM
D2: HNON; LED_3MM
D3: CINV; LED_3MM
D4: CNON; LED_3MM
DOOR: 2-PIN; 1X02
ONE_WIRE1, ONE_WIRE2, ONE_WIRE3: 3-PIN; 1X03
R1, R2: 220Ω; AXIAL-0.3
RELAY: 4-PIN; 1X04
RELAY_TERM: 4TERM; W237-4
X1: RJ45-8X; RJ45-NO-SHIELD
X2: 4TERM; W237-102
X3, X4, X5: 3TERM; W237-103

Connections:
COOL: R2.P$1 (1), RELAY.2, RELAY_TERM.2, X1.7
DATA: ONE_WIRE1.3, ONE_WIRE2.3, ONE_WIRE3.3, X1.4, X3.1, X4.1, X5.1
DOOR: DOOR.2, X1.6, X2.1
GND: D2.K (C), D4.K (C), DOOR.1, ONE_WIRE1.1, ONE_WIRE2.1, ONE_WIRE3.1, RELAY.1, RELAY_TERM.1, X1.5, X2.2, X3.3, X4.3, X5.3
HEAT: R1.P$1 (1), RELAY.3, RELAY_TERM.3, X1.8
unnamed: D1.K (C), D2.A, R1.P$2 (2)
unnamed: D3.K (C), D4.A, R2.P$2 (2)
VCC: D1.A, D3.A, ONE_WIRE1.2, ONE_WIRE2.2, ONE_WIRE3.2, RELAY.4, RELAY_TERM.4, X1.3, X3.2, X4.2, X5.2

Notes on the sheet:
ONE_WIRE

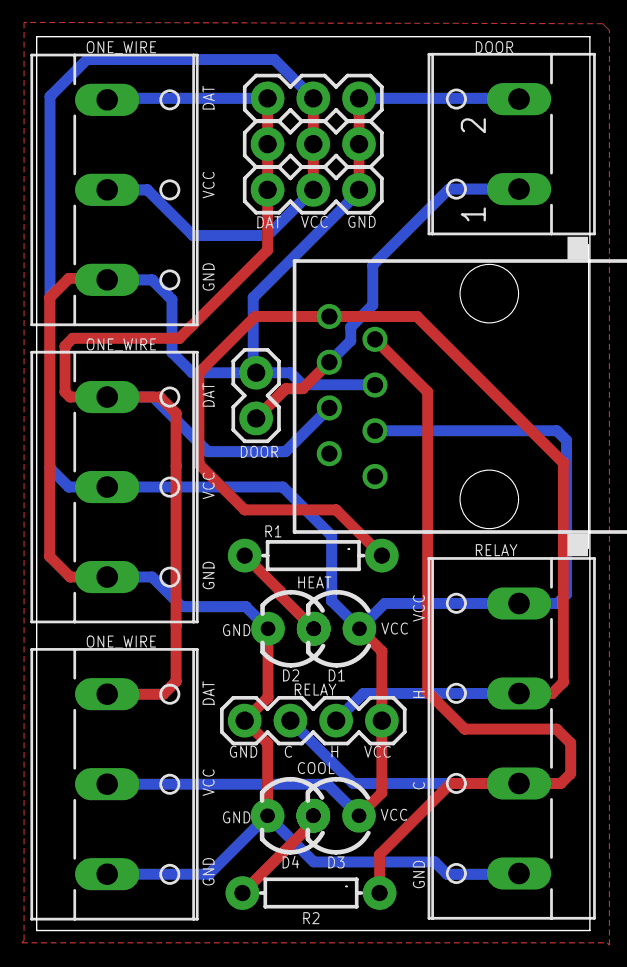
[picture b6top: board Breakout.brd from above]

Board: 2 copper layers, 30.7 x 49.7 mm, 17 parts (0 on the bottom side), 8 nets.

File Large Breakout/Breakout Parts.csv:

"Part";"Value";"Device";"Package";"Description";"MF";"MPN";"OC_FARNELL";"OC_NEWARK";"PROD_ID";"VALUE";
"D1";"HINV";"LED3MM";"LED_3MM";"LED (Generic)";"";"";"";"";"DIO-08794";"";
"D2";"HNON";"LED3MM";"LED_3MM";"LED (Generic)";"";"";"";"";"DIO-08794";"";
"D3";"CINV";"LED3MM";"LED_3MM";"LED (Generic)";"";"";"";"";"DIO-08794";"";
"D4";"CNON";"LED3MM";"LED_3MM";"LED (Generic)";"";"";"";"";"DIO-08794";"";
"DOOR";"2-PIN";"CONN_02";"1X02";"Multi connection point. Often used as Generic Header-pin footprint for 0.1 inch spaced/style header connections";"";"";"";"";"";"";
"ONE_WIRE1";"3-PIN";"CONN_03";"1X03";"Multi connection point. Often used as Generic Header-pin footprint for 0.1 inch spaced/style header connections";"";"";"";"";"XXX-00000";"455-1750-1-ND";
"ONE_WIRE2";"3-PIN";"CONN_03";"1X03";"Multi connection point. Often used as Generic Header-pin footprint for 0.1 inch spaced/style header connections";"";"";"";"";"XXX-00000";"455-1750-1-ND";
"ONE_WIRE3";"3-PIN";"CONN_03";"1X03";"Multi connection point. Often used as Generic Header-pin footprint for 0.1 inch spaced/style header connections";"";"";"";"";"XXX-00000";"455-1750-1-ND";
"R1";"220Ω";"RESISTORAXIAL-0.3";"AXIAL-0.3";"Resistor";"";"";"";"";"";"";
"R2";"220Ω";"RESISTORAXIAL-0.3";"AXIAL-0.3";"Resistor";"";"";"";"";"";"";
"RELAY";"4-PIN";"CONN_04PTH";"1X04";"Multi connection point. Often used as Generic Header-pin footprint for 0.1 inch spaced/style header connections";"";"";"";"";"CONN-09696";"";
"RELAY_TERM";"4TERM";"W237-4";"W237-4";"WAGO SCREW CLAMP";"";"";"unknown";"unknown";"";"";
"X1";"RJ45-8X";"RJ45-8X";"RJ45-NO-SHIELD";"CORCOM Modular RJ Jacks No Shield";"";"RJ45-8X";"unknown";"16R6101";"";"";
"X2";"4TERM";"W237-102";"W237-102";"WAGO SCREW CLAMP";"";"237-102";"unknown";"70K9898";"";"";
"X3";"3TERM";"W237-103";"W237-103";"WAGO SCREW CLAMP";"";"237-103";"unknown";"18M7116";"";"";
"X4";"3TERM";"W237-103";"W237-103";"WAGO SCREW CLAMP";"";"237-103";"unknown";"18M7116";"";"";
"X5";"3TERM";"W237-103";"W237-103";"WAGO SCREW CLAMP";"";"237-103";"unknown";"18M7116";"";"";

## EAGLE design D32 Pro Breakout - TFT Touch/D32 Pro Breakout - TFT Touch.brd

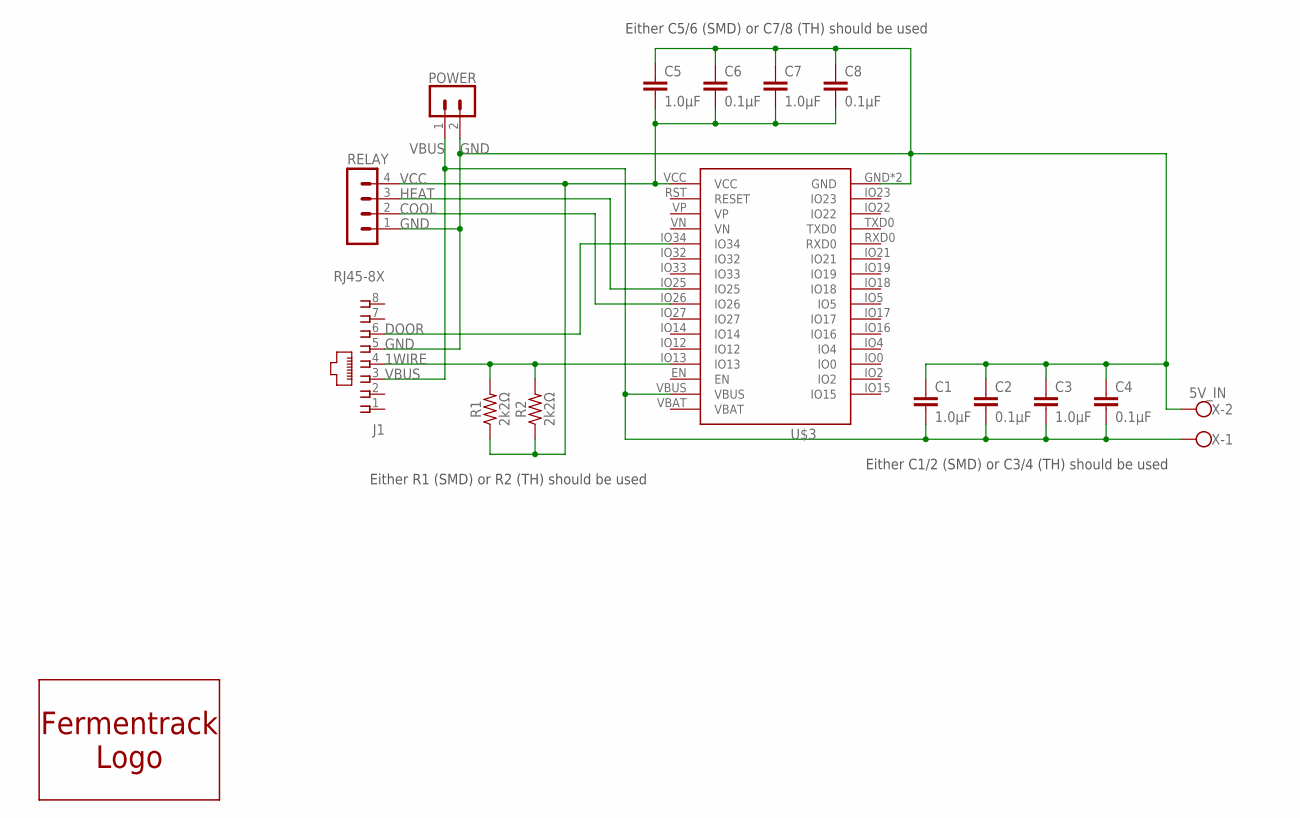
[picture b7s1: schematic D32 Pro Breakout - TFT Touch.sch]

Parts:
C1, C5: 1.0μF; SMD-1206
C2, C6: 0.1μF; SMD-1206
C3, C7: 1.0μF; CAP_PTH-2.54
C4, C8: 0.1μF; CAP_PTH-2.54
J1: RJ45-8X; RJ45-NO-SHIELD-NOLINE
R1: 2k2Ω; SMD-1206
R2: 2k2Ω; AXIAL-0.3
RELAY: HDR-4_VERT
U$3: WEMOS-D32D32_PRO_NO-BATT; D32_PRO_NO-BATT
U$5: POWER; HDR-2_VERT
U$6: LOGO_FERMENTRACKFERMENTRACK-LOGO_HALFINCH; FERMENTRACK-LOGO_SM
X: 5V_IN; W237-102

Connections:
1WIRE: J1.4, R1.2, R2.P$2 (2), U$3.IO13
COOL: RELAY.2, U$3.IO26
DOOR: J1.6, U$3.IO34
GND: C1.1, C2.1, C3.1, C4.1, C5.1, C6.1, C7.1, C8.1, J1.5, RELAY.1, U$3.GND, U$3.GND2 (GND), U$5.2, X.2
HEAT: RELAY.3, U$3.IO25
VBUS: C1.2, C2.2, C3.2, C4.2, J1.3, U$3.VBUS, U$5.1, X.1
VCC: C5.2, C6.2, C7.2, C8.2, R1.1, R2.P$1 (1), RELAY.4, U$3.VCC

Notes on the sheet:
Either C5/6 (SMD) or C7/8 (TH) should be used
Either R1 (SMD) or R2 (TH) should be used
Either C1/2 (SMD) or C3/4 (TH) should be used

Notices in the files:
parts and their libraries:
SparkFun-Boards: Licensing: Creative Commons ShareAlike 4.0 International - https://creativecommons.org/licenses/by-sa/4.0
